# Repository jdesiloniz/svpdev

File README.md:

# SVP Development Tools

A collection of development tools targetting SEGA's SVP chip found in the Mega Drive/Genesis version of Virtua Racing.

## Project structure

- **boards**: KiCAD format files of boards that allow running custom code on an actual SVP chip.
- **samples**: simple examples containing both DSP/68000 code to help developers not to start from scratch.
- **tools**: (kinda crude) tools to create software for the SVP, containing an SSP160x assembler and a ROM file manipulation tool.

## Goals

- Be able to run arbitrary code on the real SVP chip in order to research many unknowns in its behavior, and document these.
- Allow an "easy" access for people interested in this piece of videogame history to run code on it too, whether it's additional research, demos or actual new games (looking forward to it!).

# Documentation

All the research done with this project is intended to give more information about the SVP chip to allow the retrodev community to create homebrew (and run it in real hardware). As some parts of this chip are still unclear, further developments and information will be updated in the [wiki](https://github.com/jdesiloniz/svpdev/wiki) of this repository.

## License

This code is MIT-licensed. Also take into account the following conditions of use:

* Please use these tools for good. Also for fun. But good fun, not evil fun. 
* If you build something really cool (moderately cool also works for me) please drop a comment at `taiyou[at]gmail.com`.
* You're not forced, but if you use these code/tools I'd appreciate if you could acknowledge me :).

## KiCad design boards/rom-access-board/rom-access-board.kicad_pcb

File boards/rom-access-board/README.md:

# Virtua Racing ROM access board

This is the first board I designed for this project, and it's probably useless for SVP developers. Basically it exposes the original Virtua Racing ROM chip pins to a couple of connectors. I used these to put the ROM in an EEPROM reader and trick it into dumping the contents so I could figure out the pinout of the original chip. Not much else to it.

It was designed with KiCAD 5.1.

## License

The designs for these boards is open source and MIT-licensed. Also take into account the following conditions of use:

* Please use these tools for good. Also for fun. But good fun, not evil fun.
* Messing with real hardware is risky. By using these boards you are responsible for any potential issues you might find while using these designs.
* If you build something really cool (moderately cool also works for me) using these boards please drop a comment at `taiyou[at]gmail.com`.
* You're not forced, but if you use these boards in your own projects I'd appreciate if you could acknowledge me :).

## "Designed under the sun of Cadiz"

You'll find that most of my boards here have this text somewhere in their layout. I was born in [Cádiz](https://en.wikipedia.org/wiki/C%C3%A1diz), the southernmost city in Spain (and the oldest city in Western Europe). It's not a city that's usually associated to technology or these kind of projects so for me it's really important that *cool* things some of us do here related to tech are considered as part of the legacy of this town too. These designs are open source so you're free to modify them at your will, but I'd ask you kindly not to remove this label if you will. Please help us to spread the name of our wonderful city all around the tech world!

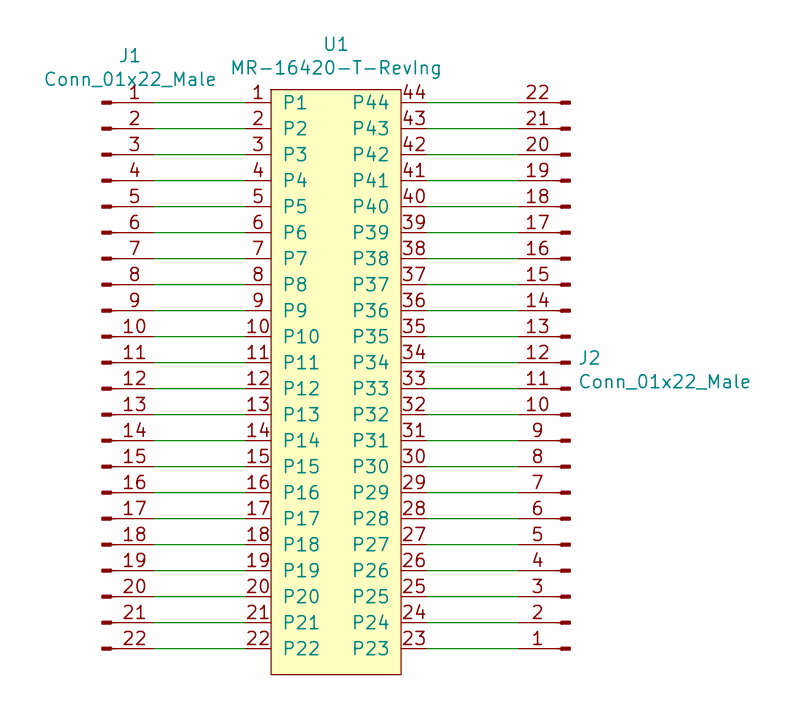
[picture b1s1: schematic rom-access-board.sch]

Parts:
J1, J2: Conn_01x22_Male; PinHeader_1x22_P2.54mm_Vertical
U1: MR-16420-T-RevIng; VR_ROM_EU_44pin

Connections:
unnamed: J1.1, U1.1
unnamed: J1.2, U1.2
unnamed: J1.3, U1.3
unnamed: J1.4, U1.4
unnamed: J1.5, U1.5
unnamed: J1.6, U1.6
unnamed: J1.7, U1.7
unnamed: J1.8, U1.8
unnamed: J1.9, U1.9
unnamed: J1.10, U1.10
unnamed: J1.11, U1.11
unnamed: J1.12, U1.12
unnamed: J1.13, U1.13
unnamed: J1.14, U1.14
unnamed: J1.15, U1.15
unnamed: J1.16, U1.16
unnamed: J1.17, U1.17
unnamed: J1.18, U1.18
unnamed: J1.19, U1.19
unnamed: J1.20, U1.20
unnamed: J1.21, U1.21
unnamed: J1.22, U1.22
unnamed: J2.1, U1.23
unnamed: J2.2, U1.24
unnamed: J2.3, U1.25
unnamed: J2.4, U1.26
unnamed: J2.5, U1.27
unnamed: J2.6, U1.28
unnamed: J2.7, U1.29
unnamed: J2.8, U1.30
unnamed: J2.9, U1.31
unnamed: J2.10, U1.32
unnamed: J2.11, U1.33
unnamed: J2.12, U1.34
unnamed: J2.13, U1.35
unnamed: J2.14, U1.36
unnamed: J2.15, U1.37
unnamed: J2.16, U1.38
unnamed: J2.17, U1.39
unnamed: J2.18, U1.40
unnamed: J2.19, U1.41
unnamed: J2.20, U1.42
unnamed: J2.21, U1.43
unnamed: J2.22, U1.44

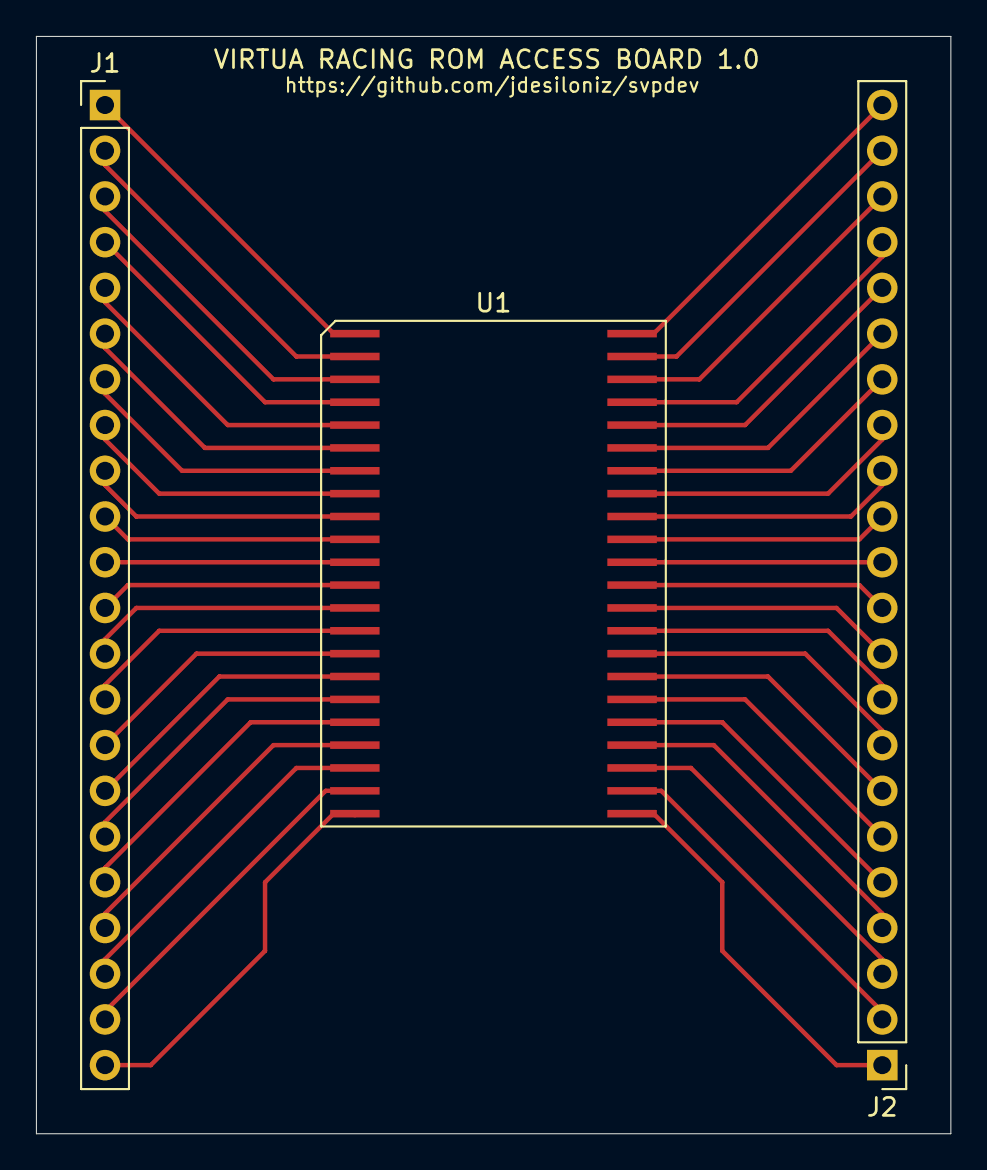
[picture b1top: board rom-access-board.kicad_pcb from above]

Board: 2 copper layers, 50.8 x 61.0 mm, 3 parts (0 on the bottom side), 44 nets.

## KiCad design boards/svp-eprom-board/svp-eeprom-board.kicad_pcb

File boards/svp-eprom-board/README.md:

# SVP EPROM board

This board attaches to the [SVP adapter board](../svp-adapter-board) and allows feeding code to the SVP from a 27C160 EPROM (or probably from any pin-compatible EEPROM like the MX29F1615PC-10 by Macronix - not tested).

Designed with KiCAD 5.1.

## Components

Even though the board is just rewiring the original ROM pins in the cartridge to the pinout of the EPROM, I added the following passive devices for good measure:

- 1x 4.7uf electrolytic capacitor.
- 1x 0.1uf (0603 package) SMD ceramic capacitor.
- 1x 0ohm resistor (1206 package).
- 1x DIP42 socket.
- 1x 44-pin header male connector (2.54mm pitch).
- Test points (optional).

I guess the bypass capacitors could be optional but the resistor is required. Anyway these are chip and not that hard to solder so please use them :).

Regarding the DIP42 socket, if you can't find these in your area just using a couple of smaller sockets (i.e.: two DIP24 sockets and cutting the extra pins from one of them) should do the trick.

There's also connectors for test pins. You probably don't need to do anything with these, but I plan to use them to measure access speeds from the SVP with my oscilloscope. But the EPROM will work just fine without them in the board.

## EPROM speeds

From what can be seen in Virtua Racing prototype boards, the SVP was meant to be used with ROMs with an access speed of 120ns or faster. The EPROMs that I used with these (27C160-100) have an access time of 100ns and they ran Virtua Racing without issues.

## Manufacturing

Any PCB manufacturer for hobbyists should be able to build this board.

## Mounting

There's not much to this board really. Just be careful with the bigger bypass capacitor polarity, and placing the EPROM in the right position.

## License

The designs for these boards is open source and MIT-licensed. Also take into account the following conditions of use:

* Please use these tools for good. Also for fun. But good fun, not evil fun.
* Messing with real hardware is risky. By using these boards you are responsible for any potential issues you might find while using these designs.
* If you build something really cool (moderately cool also works for me) using these boards please drop a comment at `taiyou[at]gmail.com`.
* You're not forced, but if you use these boards in your own projects I'd appreciate if you could acknowledge me :).

## "Designed under the sun of Cadiz"

You'll find that most of my boards here have this text somewhere in their layout. I was born in [Cádiz](https://en.wikipedia.org/wiki/C%C3%A1diz), the southernmost city in Spain (and the oldest city in Western Europe). It's not a city that's usually associated to technology or these kind of projects so for me it's really important that *cool* things some of us do here related to tech are considered as part of the legacy of this town too. These designs are open source so you're free to modify them at your will, but I'd ask you kindly not to remove this label if you will. Please help us to spread the name of our wonderful city all around the tech world!

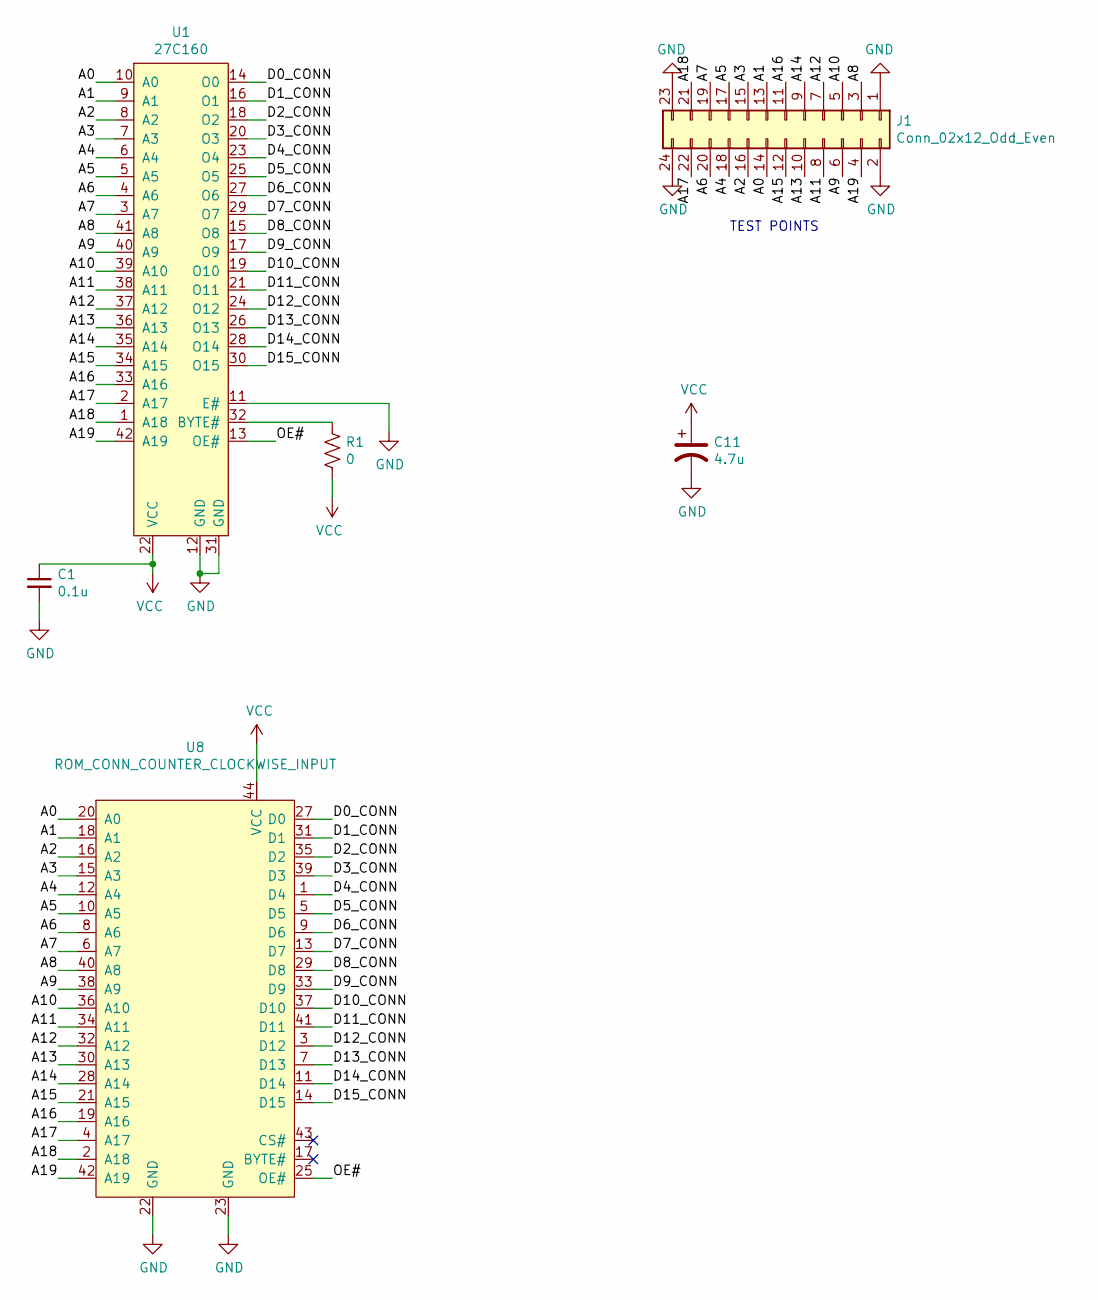
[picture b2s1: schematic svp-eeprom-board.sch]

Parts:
C1: 0.1u; C_0603_1608Metric_Pad1.08x0.95mm_HandSolder
C11: 4.7u; C_Radial_D4.0mm_H5.0mm_P1.50mm
J1: Conn_02x12_Odd_Even; PinHeader_2x12_P2.54mm_Vertical
R1: 0; R_1206_3216Metric_Pad1.30x1.75mm_HandSolder
U1: 27C160; DIP-42_W15.24mm_Socket
U8: ROM_CONN_COUNTER_CLOCKWISE_INPUT; PinHeader_2x22_P2.54mm_Vertical

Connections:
/A0: J1.14, U1.10 (A0), U8.20 (A0)
/A1: J1.13, U1.9 (A1), U8.18 (A1)
/A2: J1.16, U1.8 (A2), U8.16 (A2)
/A3: J1.15, U1.7 (A3), U8.15 (A3)
/A4: J1.18, U1.6 (A4), U8.12 (A4)
/A5: J1.17, U1.5 (A5), U8.10 (A5)
/A6: J1.20, U1.4 (A6), U8.8 (A6)
/A7: J1.19, U1.3 (A7), U8.6 (A7)
/A8: J1.3, U1.41 (A8), U8.40 (A8)
/A9: J1.6, U1.40 (A9), U8.38 (A9)
/A10: J1.5, U1.39 (A10), U8.36 (A10)
/A11: J1.8, U1.38 (A11), U8.34 (A11)
/A12: J1.7, U1.37 (A12), U8.32 (A12)
/A13: J1.10, U1.36 (A13), U8.30 (A13)
/A14: J1.9, U1.35 (A14), U8.28 (A14)
/A15: J1.12, U1.34 (A15), U8.21 (A15)
/A16: J1.11, U1.33 (A16), U8.19 (A16)
/A17: J1.22, U1.2 (A17), U8.4 (A17)
/A18: J1.21, U1.1 (A18), U8.2 (A18)
/A19: J1.4, U1.42 (A19), U8.42 (A19)
/D0_CONN: U1.14 (O0), U8.27 (D0)
/D1_CONN: U1.16 (O1), U8.31 (D1)
/D2_CONN: U1.18 (O2), U8.35 (D2)
/D3_CONN: U1.20 (O3), U8.39 (D3)
/D4_CONN: U1.23 (O4), U8.1 (D4)
/D5_CONN: U1.25 (O5), U8.5 (D5)
/D6_CONN: U1.27 (O6), U8.9 (D6)
/D7_CONN: U1.29 (O7), U8.13 (D7)
/D8_CONN: U1.15 (O8), U8.29 (D8)
/D9_CONN: U1.17 (O9), U8.33 (D9)
/D10_CONN: U1.19 (O10), U8.37 (D10)
/D11_CONN: U1.21 (O11), U8.41 (D11)
/D12_CONN: U1.24 (O12), U8.3 (D12)
/D13_CONN: U1.26 (O13), U8.7 (D13)
/D14_CONN: U1.28 (O14), U8.11 (D14)
/D15_CONN: U1.30 (O15), U8.14 (D15)
/OE#: U1.13 (OE#), U8.25 (OE#)
GND: C1.2, C11.2, J1.1, J1.2, J1.23, J1.24, U1.11 (E#), U1.12 (GND), U1.31 (GND), U8.22 (GND), U8.23 (GND)
unnamed: R1.2, U1.32 (BYTE#)
VCC: C1.1, C11.1, R1.1, U1.22 (VCC), U8.44 (VCC)

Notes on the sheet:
TEST POINTS

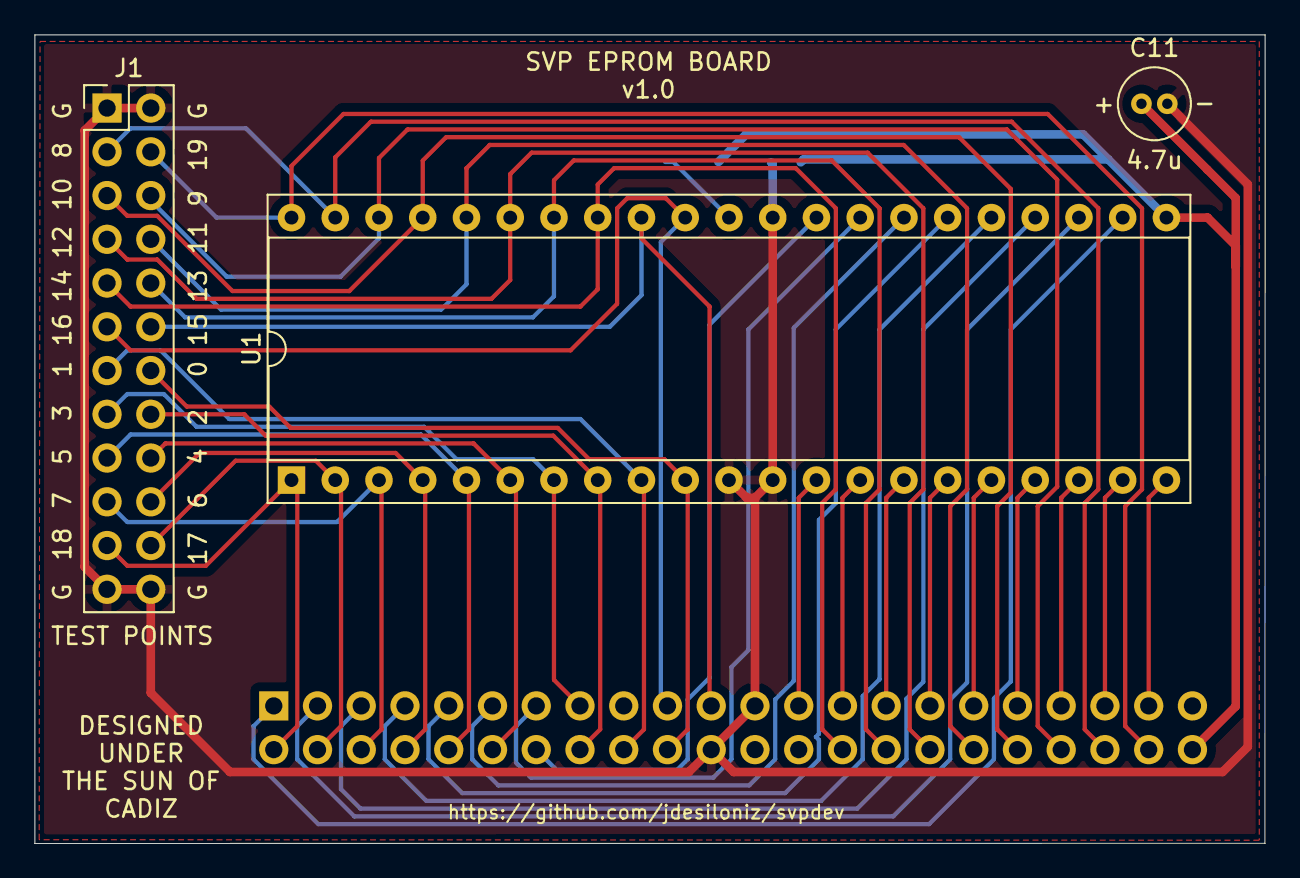
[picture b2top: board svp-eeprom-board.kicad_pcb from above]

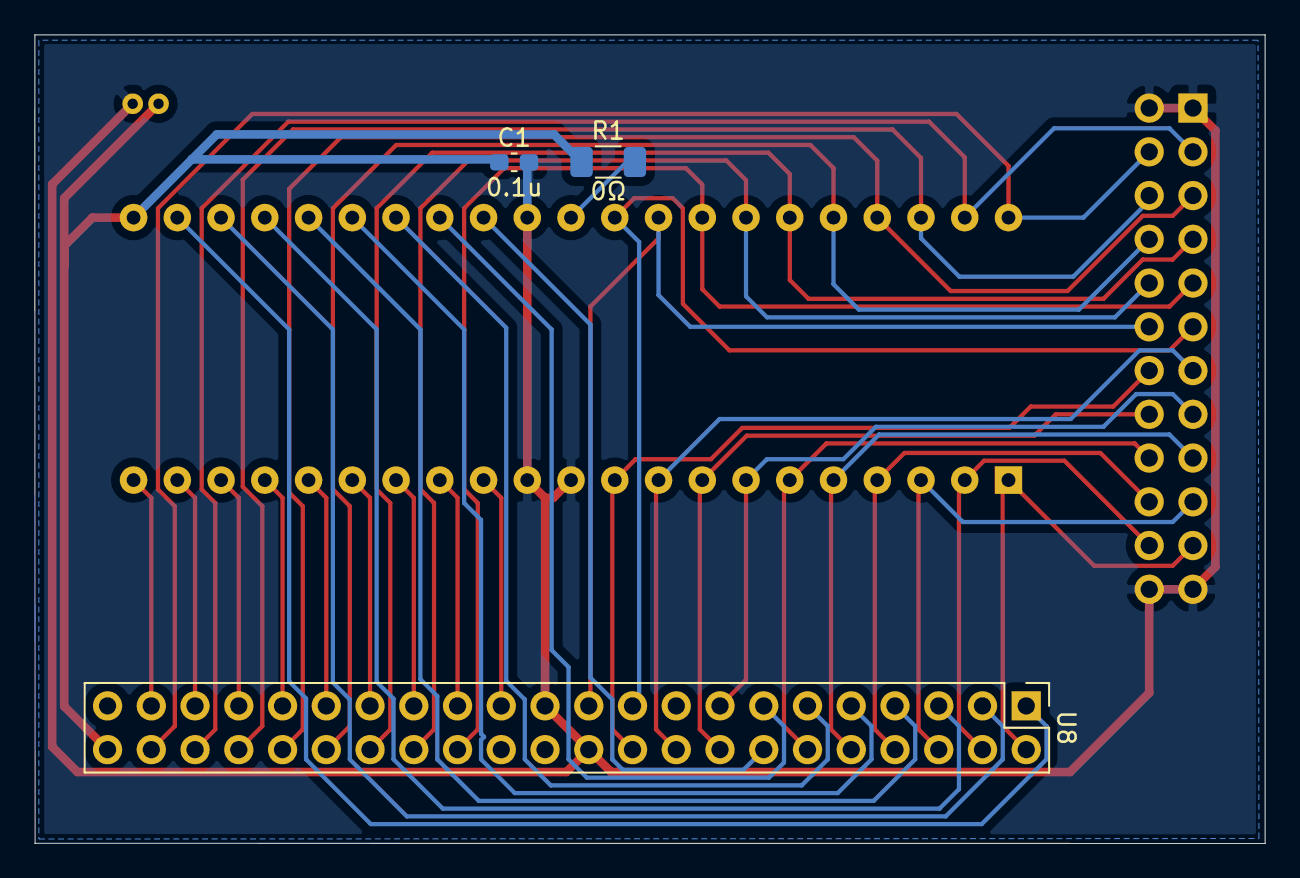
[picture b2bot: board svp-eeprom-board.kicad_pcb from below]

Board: 2 copper layers, 71.4 x 47.0 mm, 6 parts (3 on the bottom side), 40 nets.

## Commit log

2019-07-06 Added proper error handling when exceeding max binary size
2019-07-06 Formatting issue
2019-07-07 Small fix for max binary size
2019-07-12 Small fix
2019-07-25 Fixed bug with symbol table generation / printing symbol table in non-debug mode
2019-07-27 Removing OPi/LDi xxx, imm instructions with byte operators, messed up with symbol tables...
2019-07-27 Updating README
2019-07-31 Fixed another issue with symbol table generation
2019-08-01 Fixed issue with symbol table generation
2019-11-01 Feature to output binary files as hex text files
2021-01-15 Settings to load a base binary to write onto, and filling to a certain size (1M, 2M and 4M)
2021-01-15 Improved docs a bit
2021-01-16 Added SVPTOOL - restructured folders
2021-02-03 Adding EQUB to allow byte constants
2021-02-03 Clarifying bits of the assembler README
2021-02-09 Reorganizing structure - fix issue in assembler
2021-02-09 Minor fixes
2021-02-12 Adding first boards
2021-02-12 Minor fix
2021-02-13 Fix formatting issue with post-increment modes in addressing for rX registers
2021-02-19 SSP16ASM - fixed issues with labels, fixed format for LD a, A[xx] and LD A[xx], a
2021-02-19 samples - added mem reader, removed annoying LDI label after ASM update
2021-02-19 Samples - simple fix
2021-02-19 Docs - add sine table representation
2021-02-22 SSP16ASM - Fix potential add overflow issue while generating symbol table
2021-03-01 Adding sample code for SVP speed test
2021-03-01 Fixing SVP speed test README
2022-03-19 Adding decap SVP images by Richard Kaussler
2022-03-19 Additional pics
2022-03-19 Small edit
